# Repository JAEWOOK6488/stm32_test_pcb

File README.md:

# STM32F103C8T6 테스트 보드

STM32F103C8T6 기반 입출력·ADC·UART 실습 보드입니다.

[KiCad 회로도](stm32f103c8t6.kicad_sch)

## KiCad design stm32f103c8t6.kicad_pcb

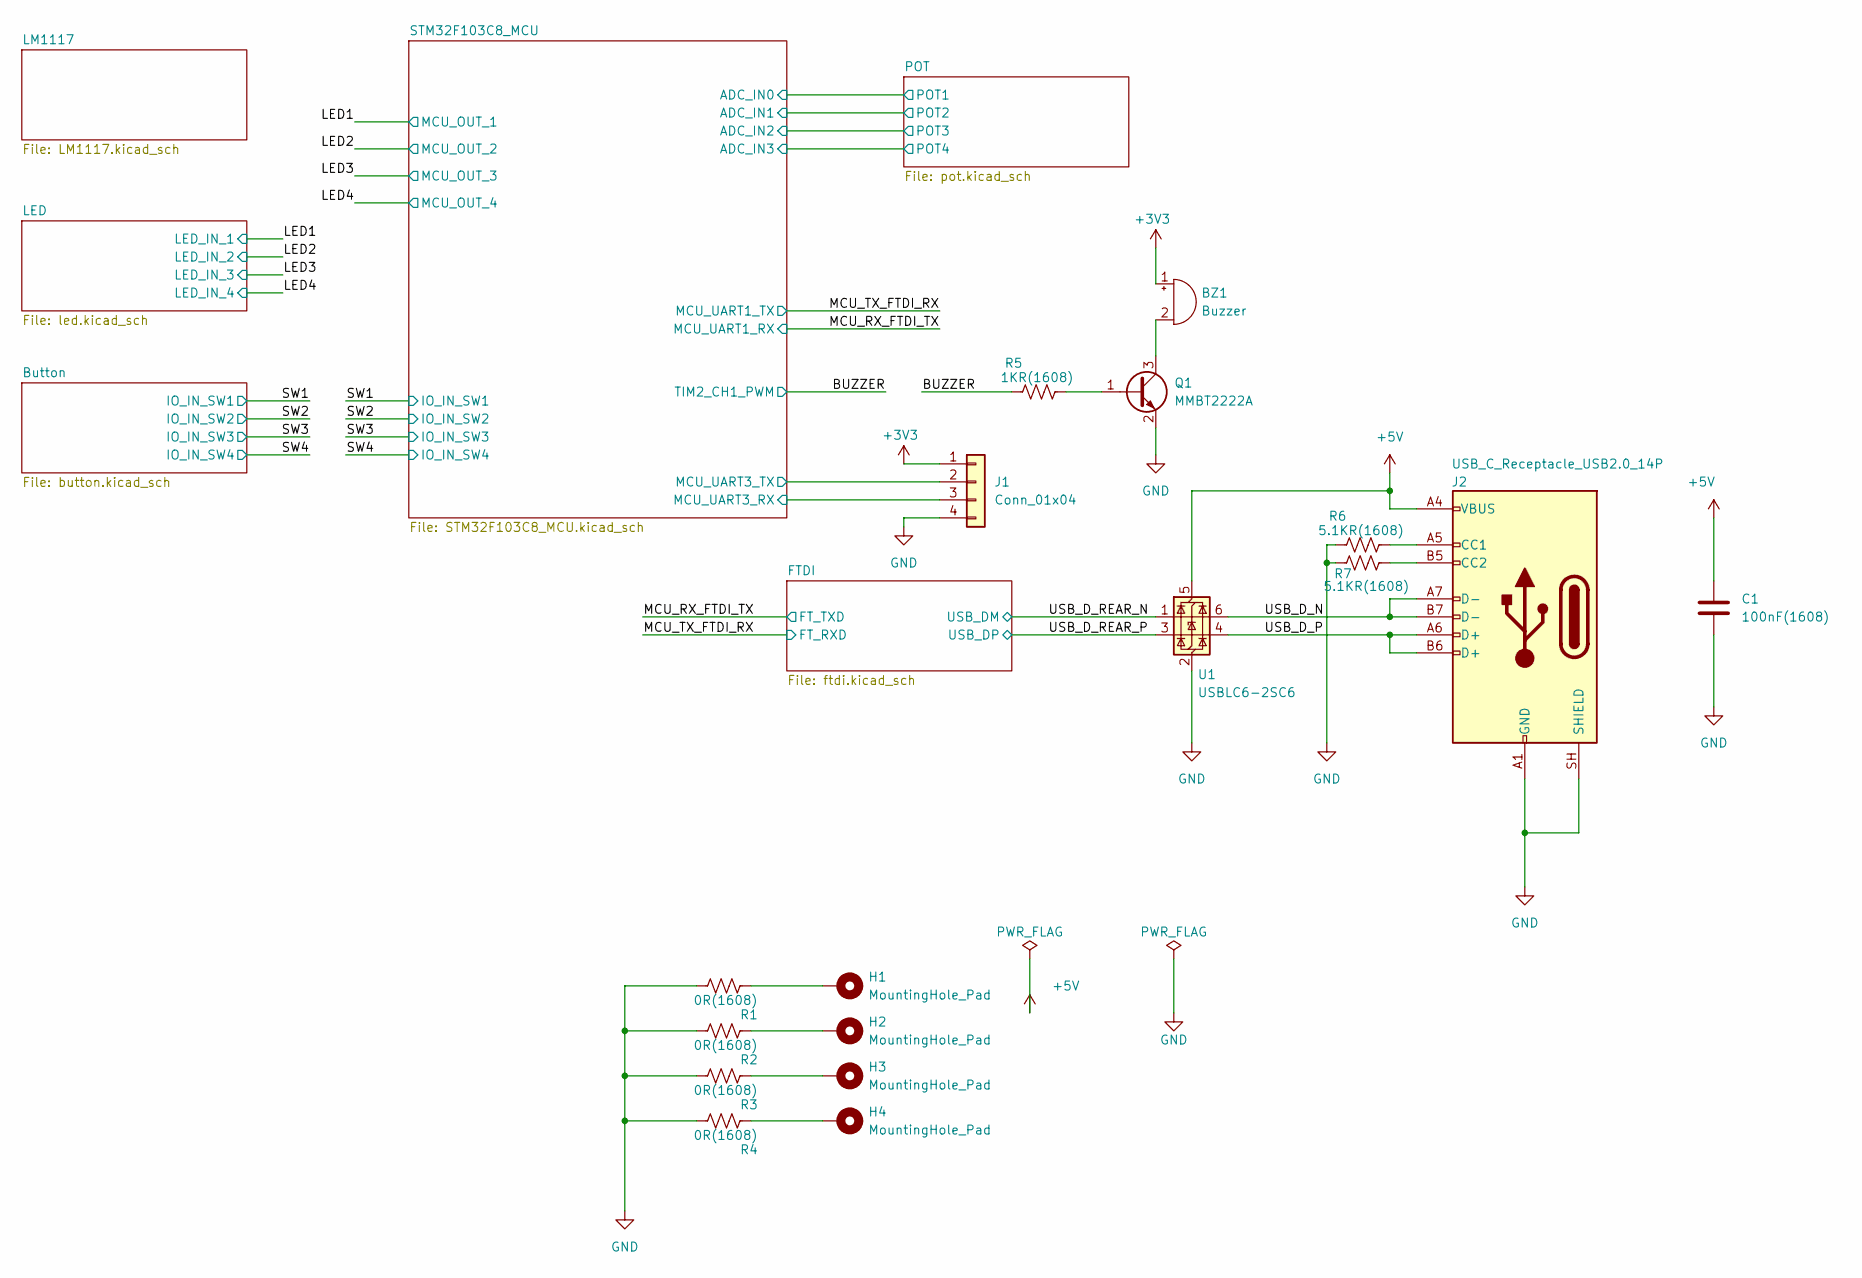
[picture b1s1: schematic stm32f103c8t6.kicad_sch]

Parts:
BZ1: Buzzer
C1: 100nF(1608); C_0603_1608Metric
H1, H2, H3, H4: MountingHole_Pad; MountingHole_3.2mm_M3_DIN965_Pad
J1: Conn_01x04; PinHeader_1x04_P2.54mm_Vertical
J2: USB_C_Receptacle_USB2.0_14P
Q1: MMBT2222A; SOT-23
R1, R2, R3, R4: 0R(1608); R_0603_1608Metric
R5: 1KR(1608); R_0603_1608Metric
R6, R7: 5.1KR(1608); R_0603_1608Metric
U1: USBLC6-2SC6; SOT-23-6

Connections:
+3V3: BZ1.1 (+), J1.1; also elsewhere on the board
+5V: C1.1, J2.A4 (VBUS), J2.A9 (VBUS), J2.B4 (VBUS), J2.B9 (VBUS), U1.5 (VBUS); also elsewhere on the board
/BUZZER: R5.1; also elsewhere on the board
/STM32F103C8_MCU/MCU_UART3_RX: J1.3; also elsewhere on the board
/STM32F103C8_MCU/MCU_UART3_TX: J1.2; also elsewhere on the board
/USB_D_N: J2.A7 (D-), J2.B7 (D-), U1.6 (I/O1)
/USB_D_P: J2.A6 (D+), J2.B6 (D+), U1.4 (I/O2)
/USB_D_REAR_N: U1.1 (I/O1); also elsewhere on the board
/USB_D_REAR_P: U1.3 (I/O2); also elsewhere on the board
GND: C1.2, J1.4, J2.A1 (GND), J2.A12 (GND), J2.B1 (GND), J2.B12 (GND), J2.SH (SHIELD), Q1.2 (E), R1.2, R2.2, R3.2, R4.2, R6.1, R7.1, U1.2 (GND); also elsewhere on the board
unnamed: BZ1.2 (-), Q1.3 (C)
unnamed: H1.1 (1_1), R1.1
unnamed: H2.1 (1_1), R2.1
unnamed: H3.1 (1_1), R3.1
unnamed: H4.1 (1_1), R4.1
unnamed: J2.A5 (CC1), R6.2
unnamed: J2.B5 (CC2), R7.2
unnamed: Q1.1 (B), R5.2

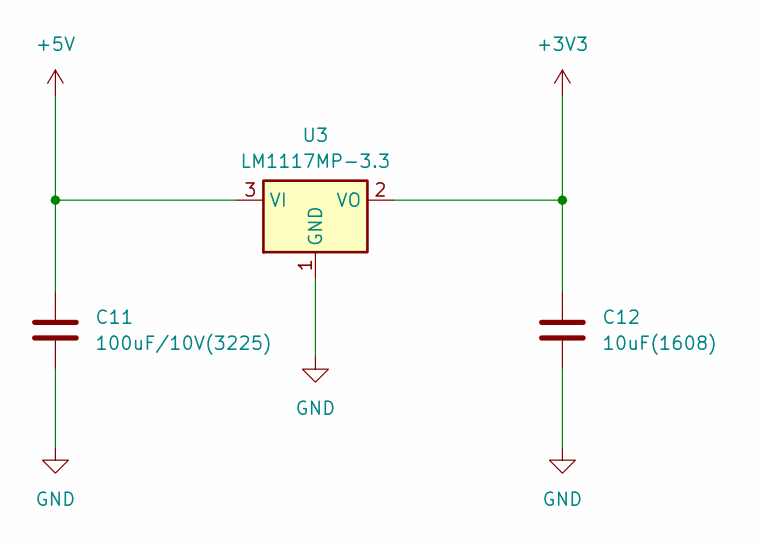
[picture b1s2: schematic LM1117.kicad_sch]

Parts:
C11: 100uF/10V(3225); C_1210_3225Metric
C12: 10uF(1608); C_0603_1608Metric
U3: LM1117MP-3.3; SOT-223-3_TabPin2

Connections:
+3V3: C12.1, U3.2 (VO); also elsewhere on the board
+5V: C11.1, U3.3 (VI); also elsewhere on the board
GND: C11.2, C12.2, U3.1 (GND); also elsewhere on the board

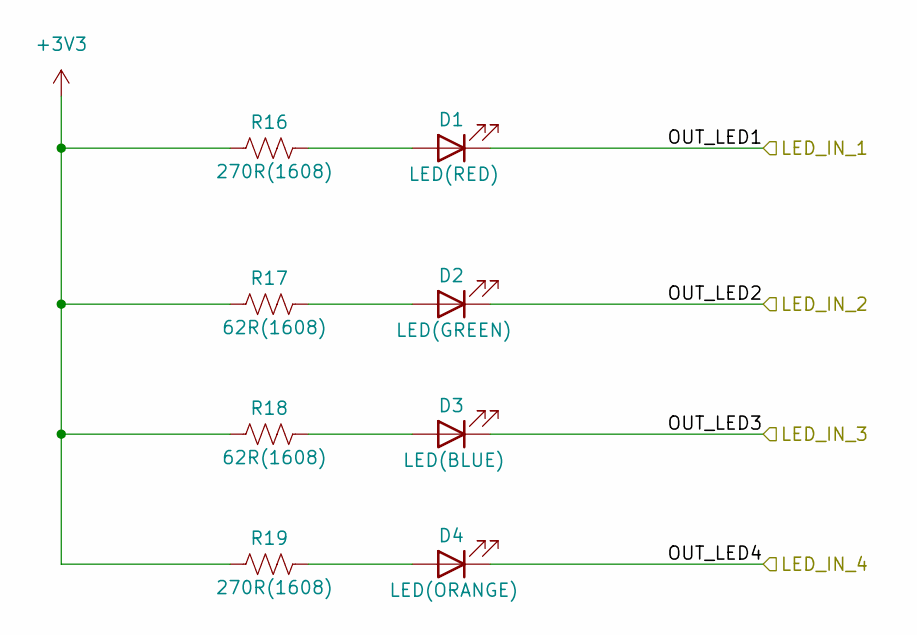
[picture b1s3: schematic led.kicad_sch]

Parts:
D1: LED(RED); LED_0603_1608Metric
D2: LED(GREEN); LED_0603_1608Metric
D3: LED(BLUE); LED_0603_1608Metric
D4: LED(ORANGE); LED_0603_1608Metric
R16, R19: 270R(1608); R_0603_1608Metric
R17, R18: 62R(1608); R_0603_1608Metric

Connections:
+3V3: R16.1, R17.1, R18.1, R19.1; also elsewhere on the board
/LED1: D1.1 (K); also elsewhere on the board
/LED2: D2.1 (K); also elsewhere on the board
/LED3: D3.1 (K); also elsewhere on the board
/LED4: D4.1 (K); also elsewhere on the board
unnamed: D1.2 (A), R16.2
unnamed: D2.2 (A), R17.2
unnamed: D3.2 (A), R18.2
unnamed: D4.2 (A), R19.2

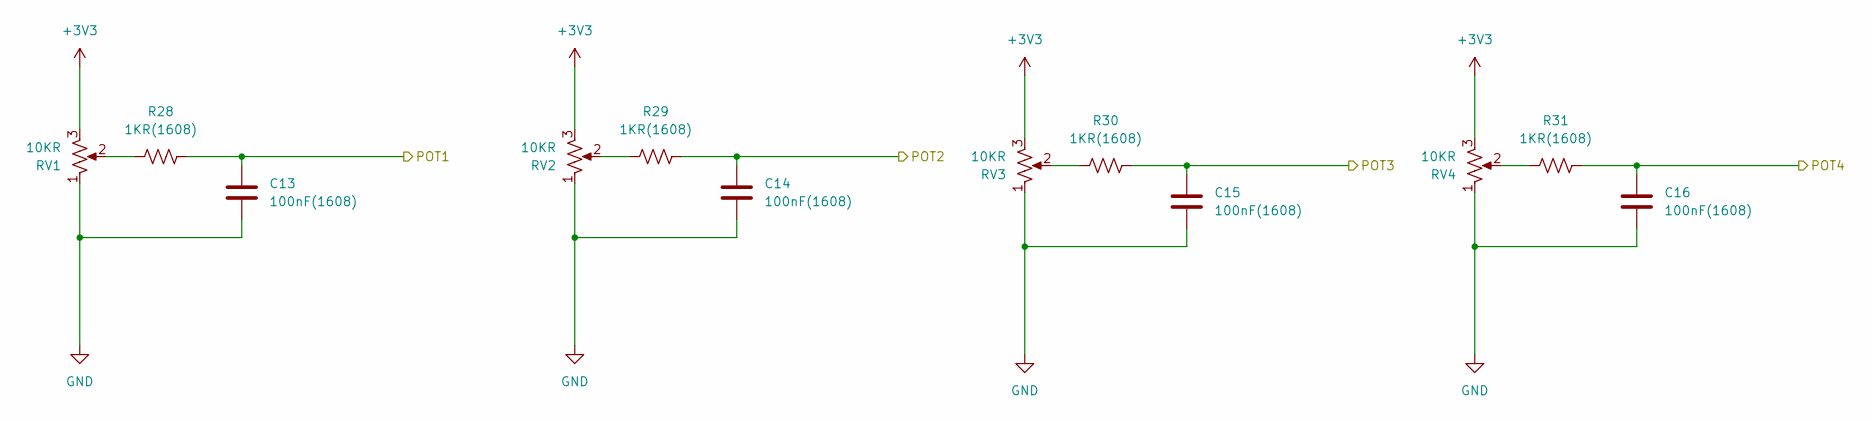
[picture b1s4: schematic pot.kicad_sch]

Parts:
C13, C14, C15, C16: 100nF(1608); C_0603_1608Metric
R28, R29, R30, R31: 1KR(1608); R_0603_1608Metric
RV1, RV2, RV3, RV4: 10KR; Potentiometer_Alps_RK09K_Single_Vertical

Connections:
+3V3: RV1.3, RV2.3, RV3.3, RV4.3; also elsewhere on the board
/POT/POT1: C13.1, R28.2; also elsewhere on the board
/POT/POT2: C14.1, R29.2; also elsewhere on the board
/POT/POT3: C15.1, R30.2; also elsewhere on the board
/POT/POT4: C16.1, R31.2; also elsewhere on the board
GND: C13.2, C14.2, C15.2, C16.2, RV1.1, RV2.1, RV3.1, RV4.1; also elsewhere on the board
unnamed: R28.1, RV1.2
unnamed: R29.1, RV2.2
unnamed: R30.1, RV3.2
unnamed: R31.1, RV4.2

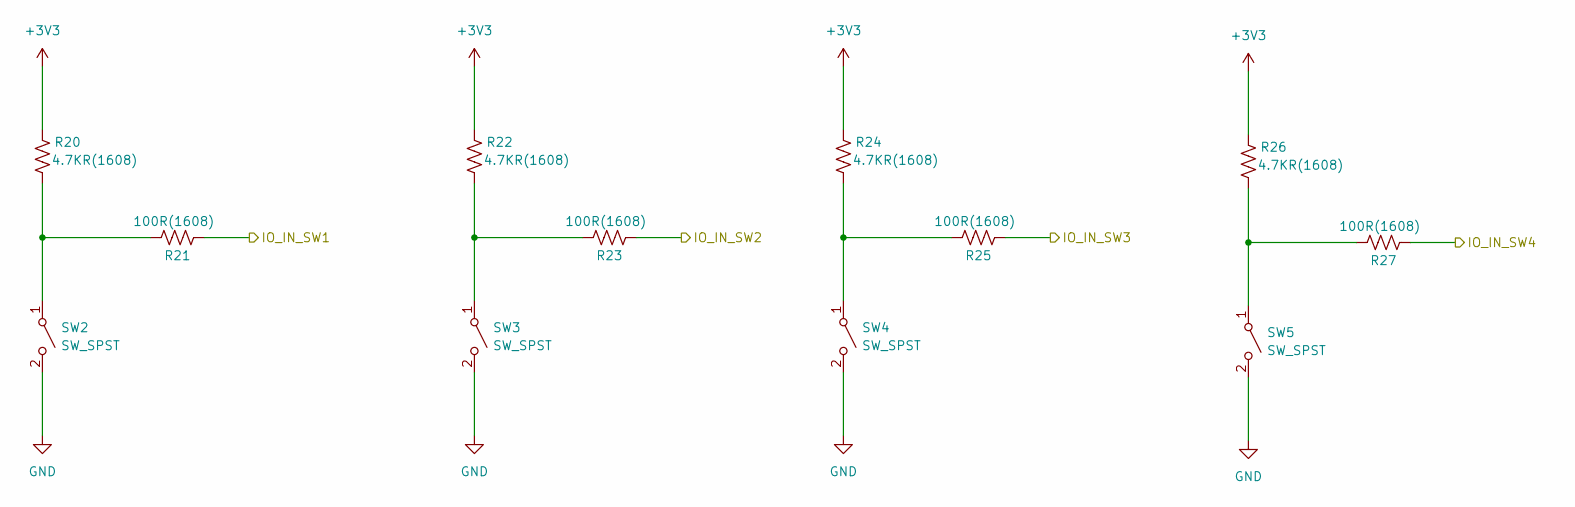
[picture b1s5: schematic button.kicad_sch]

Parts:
R20, R22, R24, R26: 4.7KR(1608); R_0603_1608Metric
R21, R23, R25, R27: 100R(1608); R_0603_1608Metric
SW2, SW3, SW4, SW5: SW_SPST; SW_PUSH_6mm_H5mm

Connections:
+3V3: R20.2, R22.2, R24.2, R26.2; also elsewhere on the board
/SW1: R21.1; also elsewhere on the board
/SW2: R23.1; also elsewhere on the board
/SW3: R25.1; also elsewhere on the board
/SW4: R27.1; also elsewhere on the board
GND: SW2.2 (B), SW3.2 (B), SW4.2 (B), SW5.2 (B); also elsewhere on the board
unnamed: R20.1, R21.2, SW2.1 (A)
unnamed: R22.1, R23.2, SW3.1 (A)
unnamed: R24.1, R25.2, SW4.1 (A)
unnamed: R26.1, R27.2, SW5.1 (A)

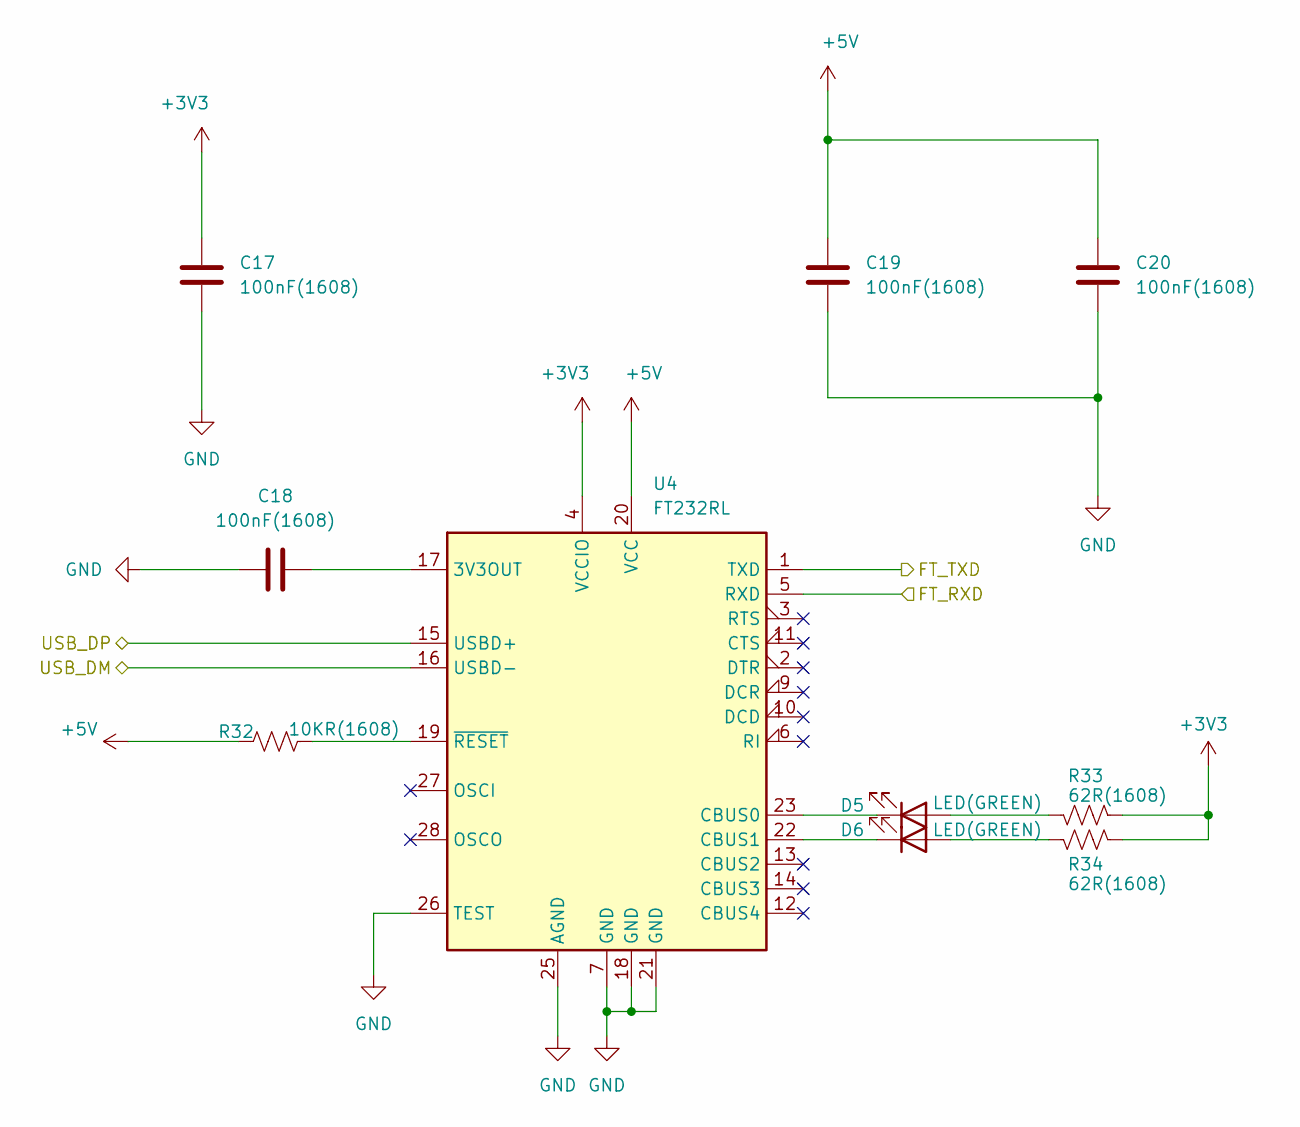
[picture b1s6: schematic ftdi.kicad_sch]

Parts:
C17, C18, C19, C20: 100nF(1608); C_0603_1608Metric
D5, D6: LED(GREEN); LED_0603_1608Metric
R32: 10KR(1608); R_0603_1608Metric
R33, R34: 62R(1608); R_0603_1608Metric
U4: FT232RL; SSOP-28_5.3x10.2mm_P0.65mm

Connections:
+3V3: C17.1, R33.2, R34.2, U4.4 (VCCIO); also elsewhere on the board
+5V: C19.1, C20.1, R32.2, U4.20 (VCC); also elsewhere on the board
/MCU_RX_FTDI_TX: U4.1 (TXD); also elsewhere on the board
/MCU_TX_FTDI_RX: U4.5 (RXD); also elsewhere on the board
/USB_D_REAR_N: U4.16 (USBD-); also elsewhere on the board
/USB_D_REAR_P: U4.15 (USBD+); also elsewhere on the board
GND: C17.2, C18.1, C19.2, C20.2, U4.7 (GND), U4.18 (GND), U4.21 (GND), U4.25 (AGND), U4.26 (TEST); also elsewhere on the board
unnamed: D5.2 (A), R33.1
unnamed: D5.1 (K), U4.23 (CBUS0)
unnamed: D6.2 (A), R34.1
unnamed: D6.1 (K), U4.22 (CBUS1)
unnamed: C18.2, U4.17 (3V3OUT)
unnamed: R32.1, U4.19 (~RESET)

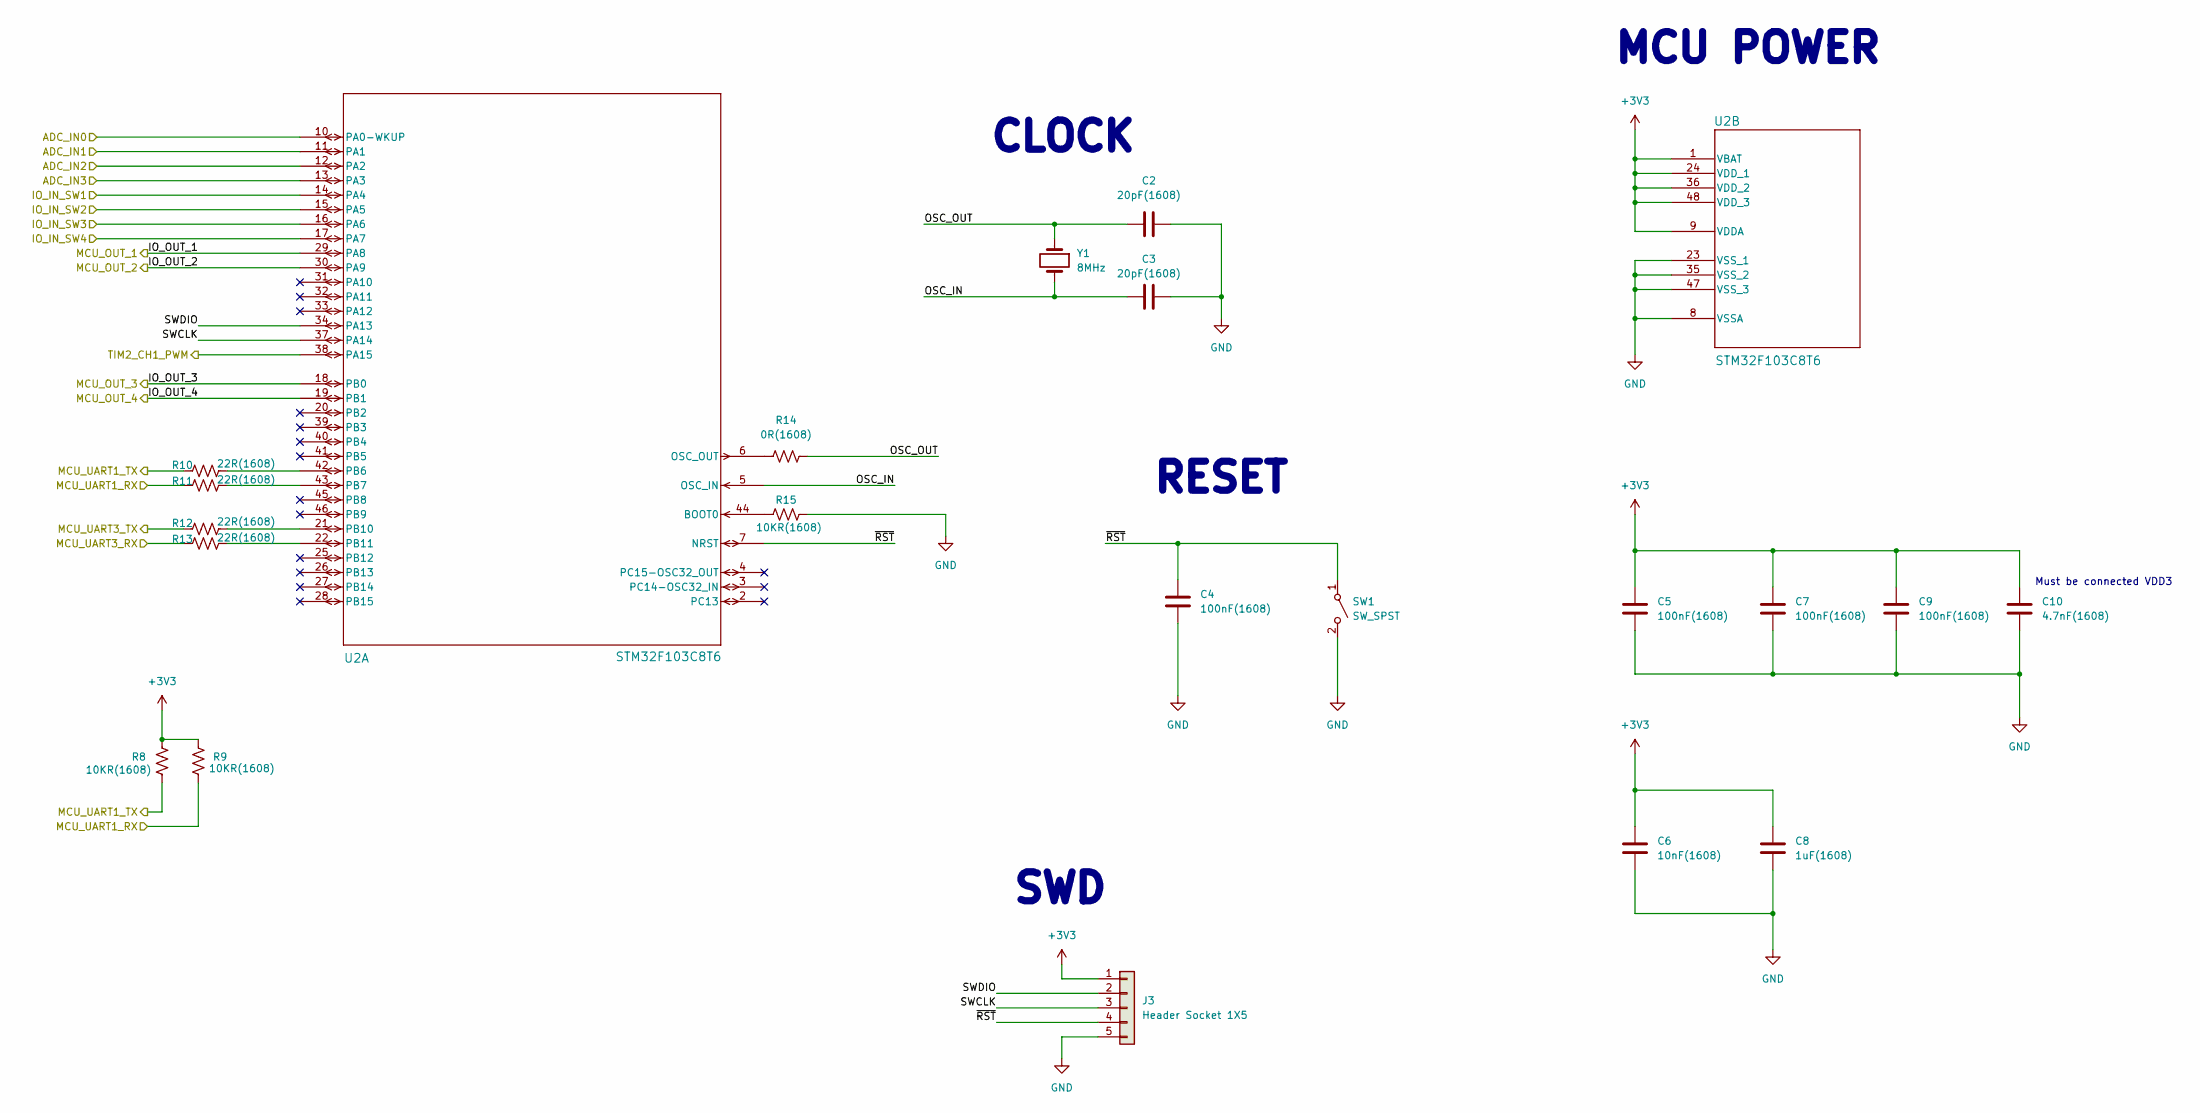
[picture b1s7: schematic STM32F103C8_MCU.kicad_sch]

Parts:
C2, C3: 20pF(1608); C_0603_1608Metric
C4, C5, C7, C9: 100nF(1608); C_0603_1608Metric
C6: 10nF(1608); C_0603_1608Metric
C8: 1uF(1608); C_0603_1608Metric
C10: 4.7nF(1608); C_0603_1608Metric
J3: Header Socket 1X5; PinHeader_1x05_P2.54mm_Vertical
R8, R9, R15: 10KR(1608); R_0603_1608Metric
R10, R11, R12, R13: 22R(1608); R_0603_1608Metric
R14: 0R(1608); R_0603_1608Metric
SW1: SW_SPST; SW_PUSH_6mm_H5mm
U2: STM32F103C8T6; LQFP48_STM
Y1: 8MHz; Crystal_SMD_HC49-SD

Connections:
+3V3: C5.1, C6.1, C7.1, C8.1, C9.1, C10.1, J3.1, R8.1, R9.1, U2.1 (VBAT), U2.9 (VDDA), U2.24 (VDD_1), U2.36 (VDD_2), U2.48 (VDD_3); also elsewhere on the board
/BUZZER: U2.38 (PA15); also elsewhere on the board
/LED1: U2.29 (PA8); also elsewhere on the board
/LED2: U2.30 (PA9); also elsewhere on the board
/LED3: U2.18 (PB0); also elsewhere on the board
/LED4: U2.19 (PB1); also elsewhere on the board
/MCU_RX_FTDI_TX: R9.2, R11.2; also elsewhere on the board
/MCU_TX_FTDI_RX: R8.2, R10.2; also elsewhere on the board
/POT/POT1: U2.10 (PA0-WKUP); also elsewhere on the board
/POT/POT2: U2.11 (PA1); also elsewhere on the board
/POT/POT3: U2.12 (PA2); also elsewhere on the board
/POT/POT4: U2.13 (PA3); also elsewhere on the board
/STM32F103C8_MCU/MCU_UART3_RX: R13.2; also elsewhere on the board
/STM32F103C8_MCU/MCU_UART3_TX: R12.2; also elsewhere on the board
/STM32F103C8_MCU/OSC_IN: C3.1, U2.5 (OSC_IN), Y1.2
/STM32F103C8_MCU/OSC_OUT: C2.2, R14.2, Y1.1
/STM32F103C8_MCU/SWCLK: J3.3, U2.37 (PA14)
/STM32F103C8_MCU/SWDIO: J3.2, U2.34 (PA13)
/STM32F103C8_MCU/~RST: C4.1, J3.4, SW1.1 (A), U2.7 (NRST)
/SW1: U2.14 (PA4); also elsewhere on the board
/SW2: U2.15 (PA5); also elsewhere on the board
/SW3: U2.16 (PA6); also elsewhere on the board
/SW4: U2.17 (PA7); also elsewhere on the board
GND: C2.1, C3.2, C4.2, C5.2, C6.2, C7.2, C8.2, C9.2, C10.2, J3.5, R15.2, SW1.2 (B), U2.8 (VSSA), U2.23 (VSS_1), U2.35 (VSS_2), U2.47 (VSS_3); also elsewhere on the board
unnamed: R15.1, U2.44 (BOOT0)
unnamed: R14.1, U2.6 (OSC_OUT)
unnamed: R10.1, U2.42 (PB6)
unnamed: R11.1, U2.43 (PB7)
unnamed: R12.1, U2.21 (PB10)
unnamed: R13.1, U2.22 (PB11)

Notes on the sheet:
SWD
CLOCK
MCU POWER
Must be connected VDD3
RESET

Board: 4 copper layers, 81 parts (0 on the bottom side), 56 nets, no tracks yet.

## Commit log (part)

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2026-02-27 Initial commit: STM32F103C8T6 KiCad project
2026-04-22 Update schematics and add LED circuit
    - Add led.kicad_sch (new LED subcircuit)
    - Update STM32F103C8_MCU schematic
    - Update top-level schematic and project file
